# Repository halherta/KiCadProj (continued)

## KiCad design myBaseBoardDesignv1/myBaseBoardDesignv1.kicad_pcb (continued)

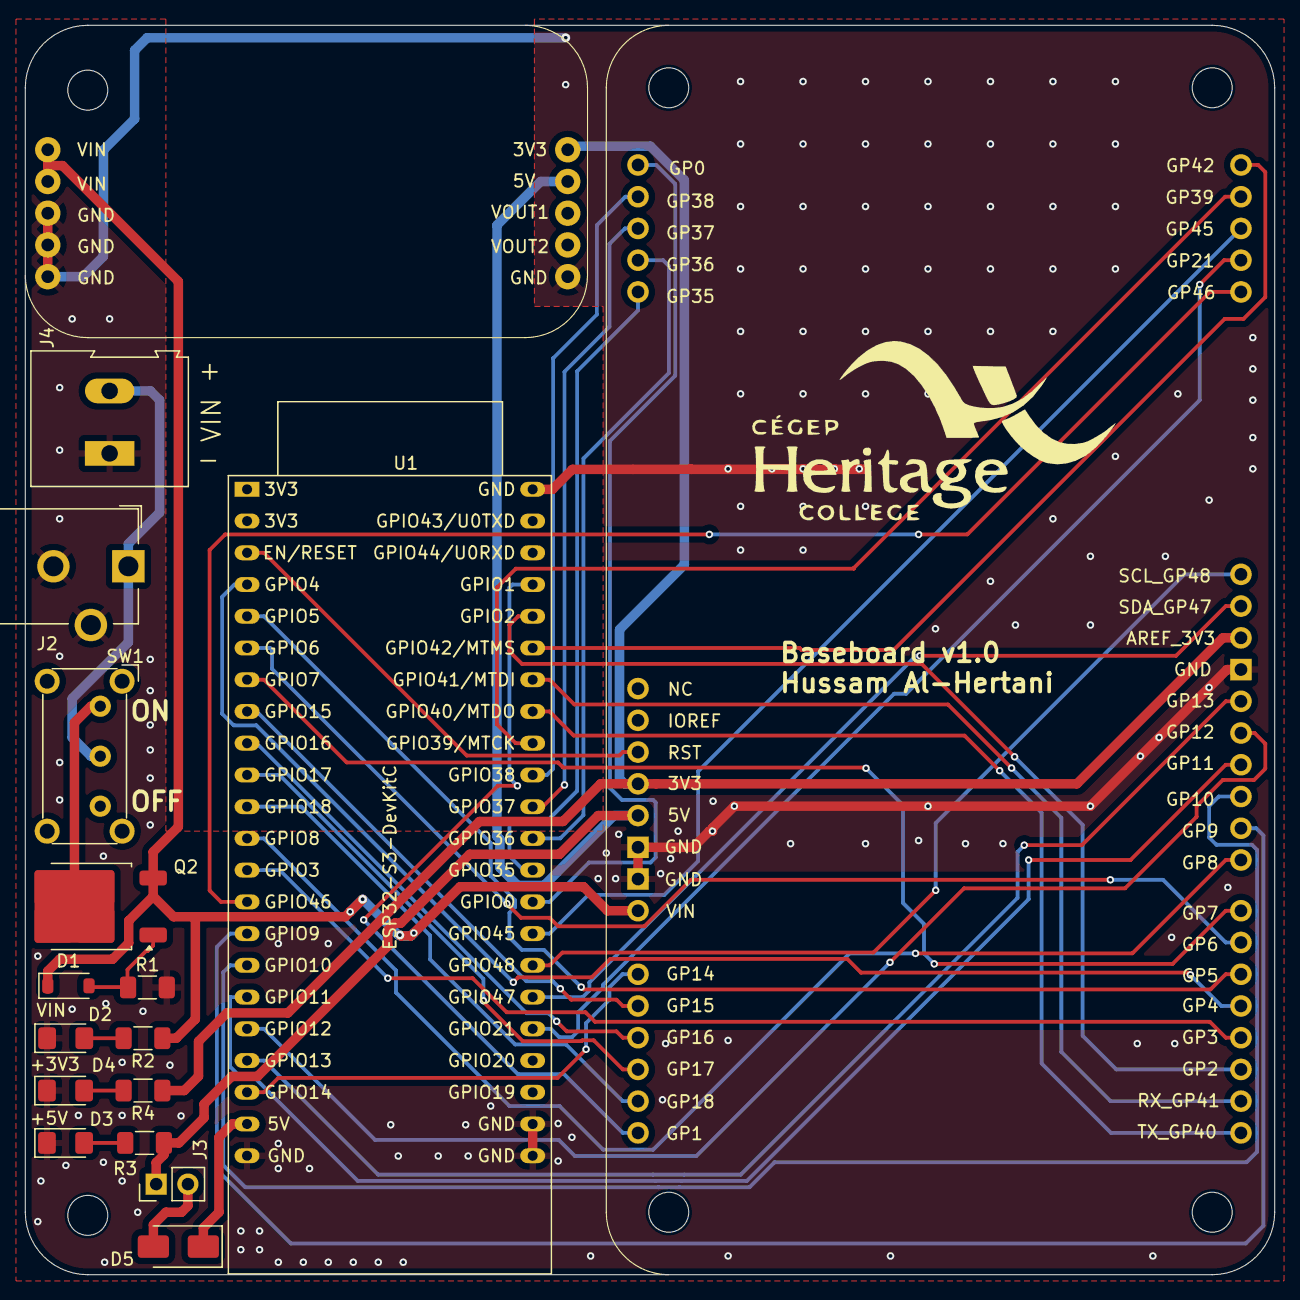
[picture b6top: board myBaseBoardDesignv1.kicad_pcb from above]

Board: 2 copper layers, 100.0 x 100.0 mm, 16 parts (0 on the bottom side), 45 nets.

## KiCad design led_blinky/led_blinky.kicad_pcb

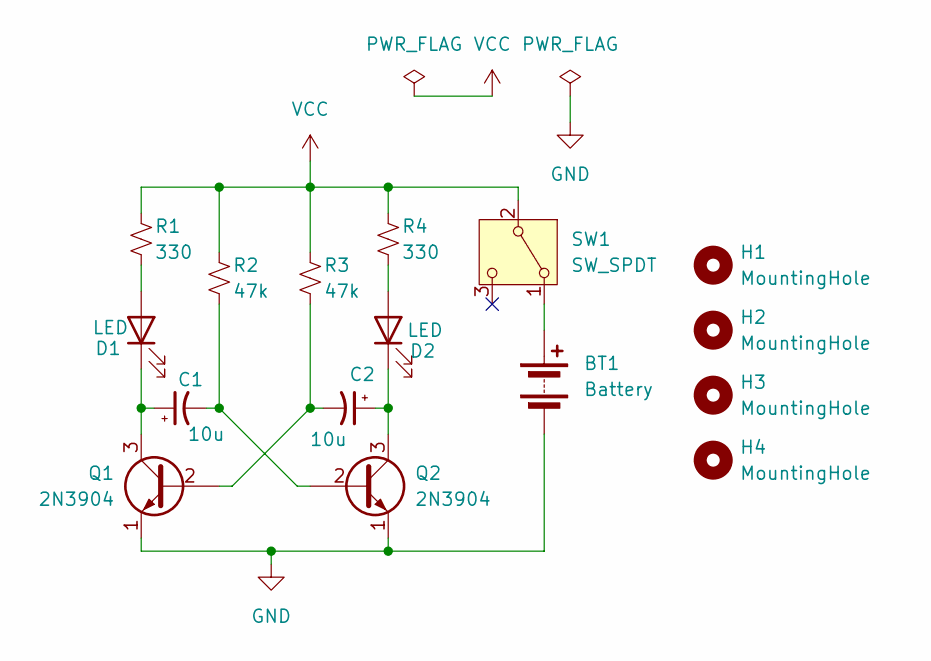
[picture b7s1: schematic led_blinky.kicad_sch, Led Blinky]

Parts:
BT1: Battery; BatteryHolder_Keystone_2479_3xAAA
C1, C2: 10u; CP_Radial_D6.3mm_P2.50mm
D1, D2: LED; LED_D5.0mm
H1, H2, H3, H4: MountingHole; MountingHole_3.2mm_M3
Q1, Q2: 2N3904; TO-92_Inline
R1, R4: 330; R_Axial_DIN0207_L6.3mm_D2.5mm_P10.16mm_Horizontal
R2, R3: 47k; R_Axial_DIN0207_L6.3mm_D2.5mm_P10.16mm_Horizontal
SW1: SW_SPDT; SW_E-Switch_EG1224_SPDT_Angled

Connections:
GND: BT1.2 (-), Q1.1 (E), Q2.1 (E)
unnamed: BT1.1 (+), SW1.1 (A)
unnamed: D1.2 (A), R1.2
unnamed: C1.1, D1.1 (K), Q1.3 (C)
unnamed: D2.2 (A), R4.2
unnamed: C2.1, D2.1 (K), Q2.3 (C)
unnamed: C2.2, Q1.2 (B), R3.2
unnamed: C1.2, Q2.2 (B), R2.2
VCC: R1.1, R2.1, R3.1, R4.1, SW1.2 (B)

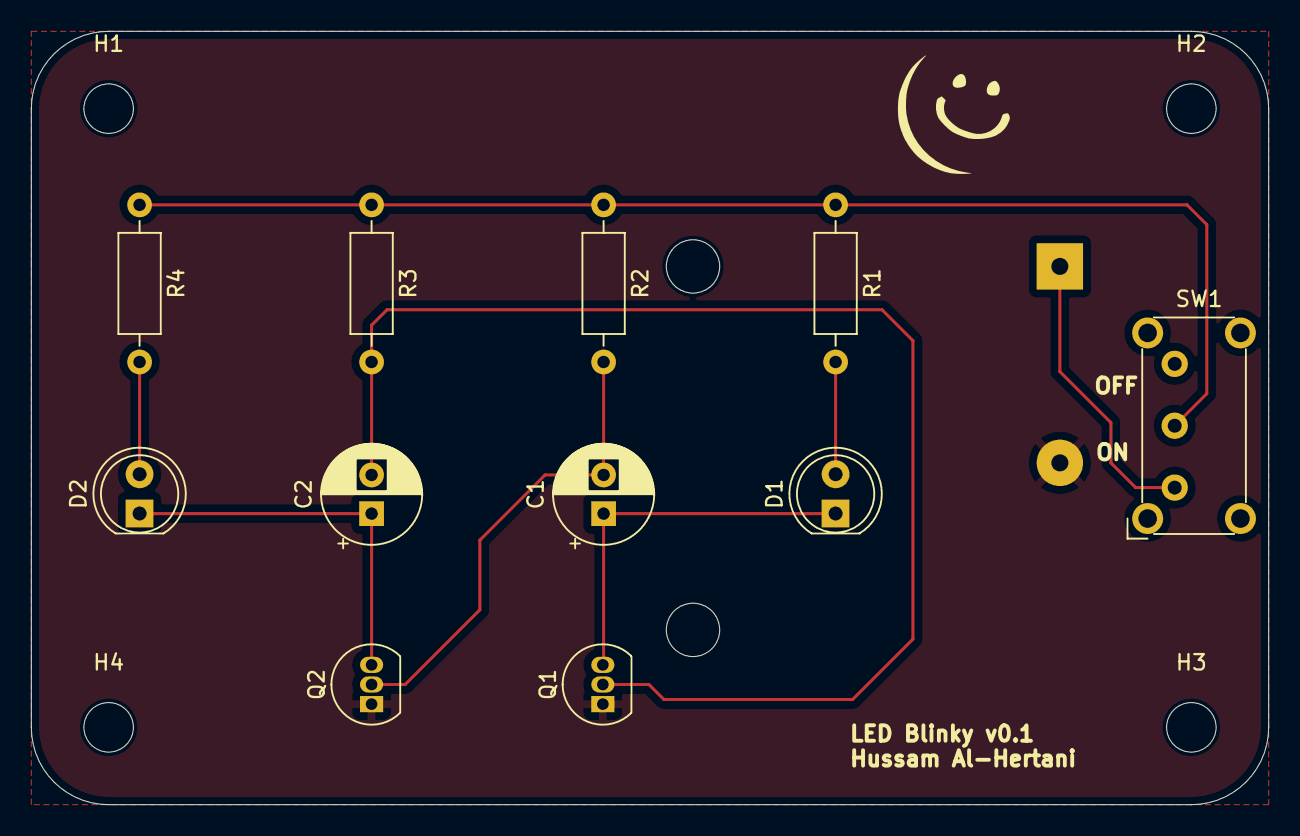
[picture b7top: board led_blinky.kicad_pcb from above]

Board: 2 copper layers, 80.0 x 50.0 mm, 16 parts (1 on the bottom side), 9 nets.

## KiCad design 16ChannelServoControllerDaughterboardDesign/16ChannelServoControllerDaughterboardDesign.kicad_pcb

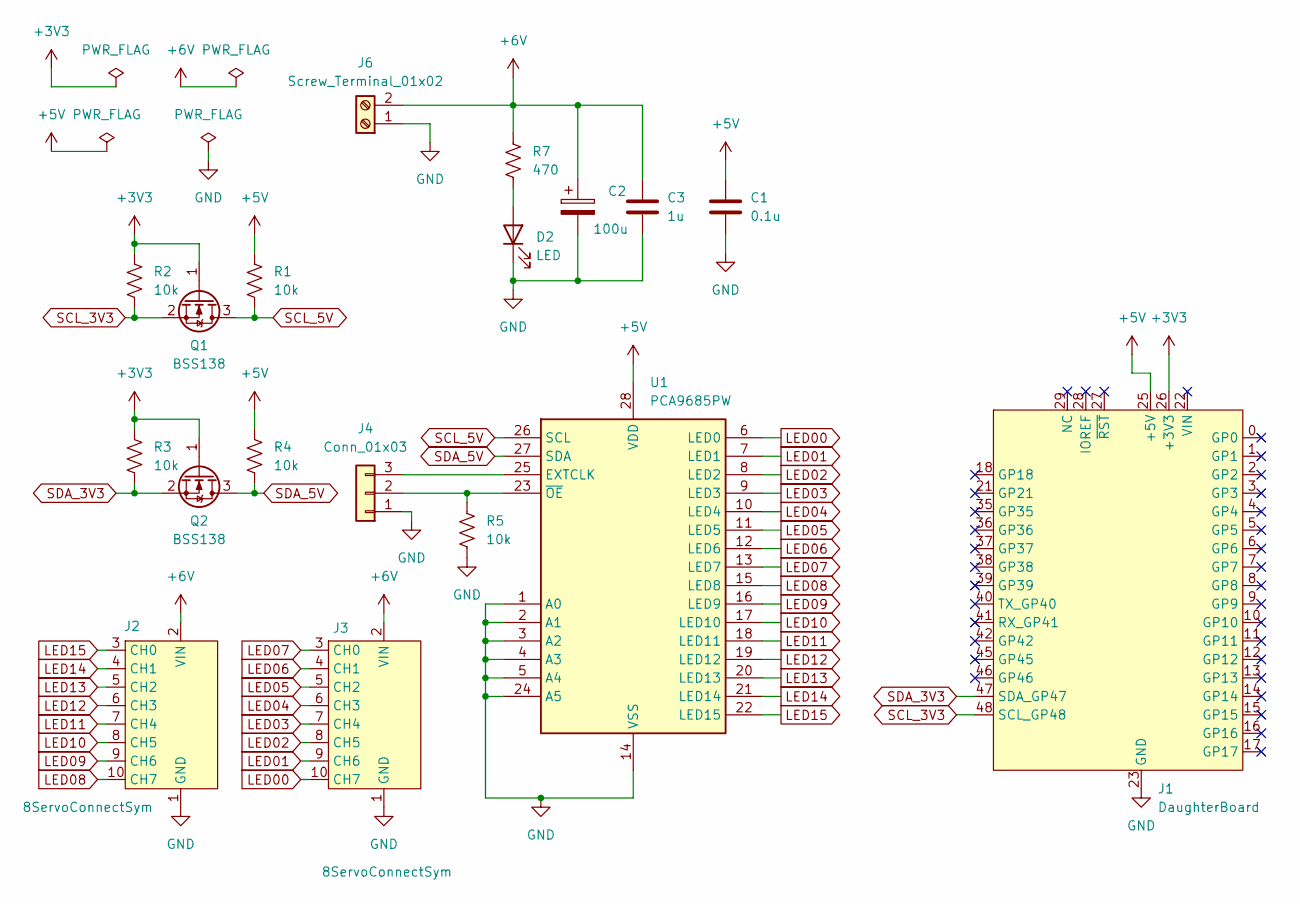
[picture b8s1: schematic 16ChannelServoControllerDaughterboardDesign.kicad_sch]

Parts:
C1: 0.1u; C_1206_3216Metric_Pad1.33x1.80mm_HandSolder
C2: 100u; CP_Elec_6.3x7.7
C3: 1u; C_1206_3216Metric_Pad1.33x1.80mm_HandSolder
D2: LED; LED_1206_3216Metric_Pad1.42x1.75mm_HandSolder
J1: DaughterBoard; DaughterBoardTemplate
J2, J3: 8ServoConnectSym; 8ServoConnect
J4: Conn_01x03; PinHeader_1x03_P2.54mm_Vertical
J6: Screw_Terminal_01x02; TerminalBlock_Altech_AK300-2_P5.00mm
Q1, Q2: BSS138; SOT-23
R1, R2, R3, R4, R5: 10k; R_1206_3216Metric_Pad1.30x1.75mm_HandSolder
R7: 470; R_1206_3216Metric_Pad1.30x1.75mm_HandSolder
U1: PCA9685PW; TSSOP-28_4.4x9.7mm_P0.65mm

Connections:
+3V3: J1.26 (+3V3), J1.32 (+3V3), Q1.1 (G), Q2.1 (G), R2.1, R3.1
+5V: C1.1, J1.25 (+5V), R1.1, R4.1, U1.28 (VDD)
+6V: C2.1, C3.1, J2.2 (VIN), J3.2 (VIN), J6.2, R7.1
GND: C1.2, C2.2, C3.2, D2.1 (K), J1.23 (GND), J1.24 (GND), J1.30 (GND), J2.1 (GND), J3.1 (GND), J4.1, J6.1, R5.2, U1.1 (A0), U1.2 (A1), U1.3 (A2), U1.4 (A3), U1.5 (A4), U1.14 (VSS), U1.24 (A5)
LED00: J3.10 (CH7), U1.6 (LED0)
LED01: J3.9 (CH6), U1.7 (LED1)
LED02: J3.8 (CH5), U1.8 (LED2)
LED03: J3.7 (CH4), U1.9 (LED3)
LED04: J3.6 (CH3), U1.10 (LED4)
LED05: J3.5 (CH2), U1.11 (LED5)
LED06: J3.4 (CH1), U1.12 (LED6)
LED07: J3.3 (CH0), U1.13 (LED7)
LED08: J2.10 (CH7), U1.15 (LED8)
LED09: J2.9 (CH6), U1.16 (LED9)
LED10: J2.8 (CH5), U1.17 (LED10)
LED11: J2.7 (CH4), U1.18 (LED11)
LED12: J2.6 (CH3), U1.19 (LED12)
LED13: J2.5 (CH2), U1.20 (LED13)
LED14: J2.4 (CH1), U1.21 (LED14)
LED15: J2.3 (CH0), U1.22 (LED15)
unnamed: D2.2 (A), R7.2
unnamed: J4.2, R5.1, U1.23 (~OE)
unnamed: J4.3, U1.25 (EXTCLK)
SCL_3V3: J1.48 (SCL_GP48), Q1.2 (S), R2.2
SCL_5V: Q1.3 (D), R1.2, U1.26 (SCL)
SDA_3V3: J1.47 (SDA_GP47), Q2.2 (S), R3.2
SDA_5V: Q2.3 (D), R4.2, U1.27 (SDA)

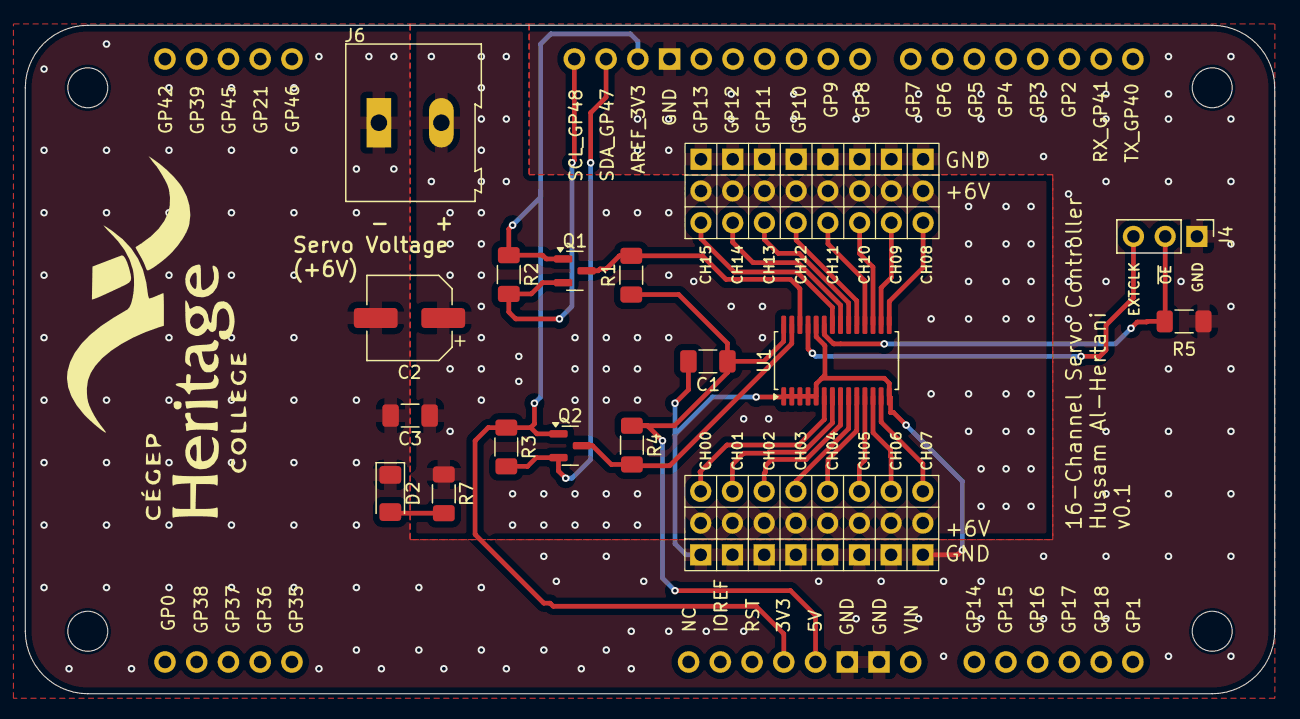
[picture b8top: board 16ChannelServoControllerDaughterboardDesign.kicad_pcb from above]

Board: 2 copper layers, 100.0 x 53.5 mm, 18 parts (0 on the bottom side), 27 nets.

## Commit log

2024-04-01 Let's get this party started
2024-04-02 Updated Tue Apr 2 2024 18:42
2024-04-07 commit Apr 7 2024
2024-04-27 Sat: Apr 27 Added Dual H-Bridge Daughterboard and fixed railsplitter
2024-04-27 Sat Apr 27: fixed a few things. Finalized v0.2 baseboard and powerboard. Added logos.
2024-05-01 Added an improved version 0.2 Stereo Amp with heatsinks
2024-05-05 Added16 Channel Servo controller Design
2024-05-08 created _latest gerber sets and added digikey boms. Also did some project cleanup WedMay82024
2024-05-09 updated bom for 16Channel Servo WedMay82024
2024-06-28 added rev1 of Baseboard with updated Gerbers and Digikey BOM
2024-09-23 two more projects ..HeartLEDTHT & TPA3122D2_Amplifier
2024-09-23 updates to powerboard and h-bridge...added thermal reliefs
2024-10-02 latest updates as of Oct 2nd 2024
2024-10-16 Create README.md
    # ESP32-S3 Arduino Uno board
2024-10-18 latest updates
2024-10-18 latest updates again
2024-10-18 Drop files from .gitignore
